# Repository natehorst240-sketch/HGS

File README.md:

# HGS-Linux

A Linux/cross-platform re-implementation of the **Agusta A109S / A109N HGS**
ground-station software (`Hgs_cpp.exe`, MFC-era Windows app) that reads IDS/DAU
downloads from the aircraft.

## Status

The `.HG*` download file format has been **reverse-engineered and verified
value-for-value against the original application** (see [FORMAT.md](FORMAT.md)):

| Section | Status |
|---------|--------|
| Parameter catalog (exceedance/fault dictionary) | decoded |
| Fault Log (first/last occurrence, count) | decoded, 16/16 events verified |
| AFCS Fault Log | decoded |
| Cumulative Log (flights, TSN/TBO, cycle counts, chip D.A., ...) | decoded, 43/43 fields verified |
| Power Assurance Log | decoded, record verified (stored fields; app-side "Calc" columns are computed, not stored) |
| Time History (1 Hz N1/N2/TRQ/TOT/CLP/NR) | decoded, verified |
| Exceedance *event* records (Max Peak/Duration) | layout unknown — need a download containing a real exceedance |
| IDS Status Log | not present in sample |
| **Live serial download protocol (9600,n,8,1)** | **fully reverse-engineered from a live capture — see reverse/PROTOCOL.md** |

## Serial protocol — DONE

Captured live from a real A109 download and validated: 25-byte space-padded
ASCII messages, stop-and-wait (downloader sends `DOWNLOAD LOGS`, DAU streams
each `.HG` record, downloader acks each with `TRANSMISSION OK`). Concatenated
records == the `.HG` file. The stick firmware (`firmware/dau_protocol.py`) is a
complete, real implementation — replayed against the captured frames it
reassembles the download byte-for-byte (589,237 bytes, exact match). Spec in
`reverse/PROTOCOL.md`; capture tools in `reverse/frida/`.

Key encoding facts: everything numeric is **BCD**; labels are 25-byte
space-padded ASCII; sequence IDs are the only plain big-endian uint16s.

## Layout

- `hgs/hg6.py` — the download-file parser (the important part)
- `hgs/ui.py` — PySide6 viewer with the original app's seven Data View tabs
- `hgs/protocol.py` — serial download state-machine skeleton (`TODO(protocol)`)
- `hgs/config.py` — INI config replacing the original's registry keys
- `FORMAT.md` — byte-level file-format specification
- `sandbox/` — Wine sandbox for the original `.exe` on Linux: `setup.sh`, `run.sh --tap /dev/ttyUSB0` or `--sim` (serial tap + DAU simulator, `--wireshark` live), `sniff.py` terminal sniffer, `wireshark/hgs.lua` dissector, `selftest.py`
- `sample-data/` — a real download (S/N 22366) + decoded CSV exports

## Run (Linux)

```bash
python3 -m venv .venv && source .venv/bin/activate
pip install -r requirements.txt
python -m hgs        # File -> Open -> sample-data/22366_260707_A1.HG6
```

Parsing works headless too:

```python
from hgs import hg6
p = hg6.parse_file("sample-data/22366_260707_A1.HG6")
print(p.cumulative, p.faults, len(p.time_history))
```

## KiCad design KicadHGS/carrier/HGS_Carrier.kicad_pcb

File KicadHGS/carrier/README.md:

# HGS Download Stick — RS-232 carrier

Pico-format carrier that sits under the **Waveshare ESP32-S3-Touch-LCD-1.9
(SKU 30939)** and gives it a DE9 RS-232 port for the A109 DAU maintenance
connector.

> **This revision is a deliberately minimal 3-wire MAX3232 straight-through.**
> An earlier design had jumpers (JP1–JP3), a 2N7002 for FUNCTION SEL, D1/D2 TVS,
> 47 Ω series resistors, and a CTS sense line. Those were **removed** — the real
> captured download is plain 3-wire stop-and-wait (see `../../reverse/PROTOCOL.md`),
> so none of them are needed. If you're reading an older description mentioning
> jumpers/MOSFET/TVS, it's stale; the netlist below is the truth.

| File | What it is |
|---|---|
| `HGS_Carrier.kicad_sch` | the schematic — open this |
| `HGS_Carrier.kicad_sym` | project symbol for the module (40 pins, real ESP32 names) |
| `gen_schematic.py` | generator that produced the schematic — edit this, not the .kicad_sch |
| `bom.csv`, `net.net`, `erc.rpt` | exports, regenerate any time with `kicad-cli` |
| `upstream/` | mtguerreiro's MAX3232 sheet + licence (see Attribution) |

## The circuit (as actually netlisted)

Verified from `net.net`, not the prose:

```
ESP32-S3-Touch-LCD-1.9 (J1)     MAX3232 (U1) on 3V3        DE9 (J2, male DTE)
  IO16  (J1 pin 15) ----------- T1IN(11) -> T1OUT(14) ---- pin 3  TXD  -> DAU RXD
  IO18  (J1 pin 17) <----------- R1OUT(12) <- R1IN(13) ---- pin 2  RXD  <- DAU TXD
  GND (all 8 module GND) ------- GND(15) ----------------- pin 5  GND + shell
  3V3   (J1 pin 36) ----------- VCC(16)
```

- **U1 MAX3232**, VCC on **+3V3 only** (never 5 V — the S3 is not 5 V tolerant),
  charge-pump caps **C1–C5 100 nF** (C1±, C2±, V+, V−).
- **9600 baud, 8N1** (`Serial1.begin(9600, SERIAL_8N1, RX=IO18, TX=IO16)` in
  firmware) — matches the original app's `9600,n,8,1`.
- The firmware uses **Serial1 on IO16/IO18**, a second UART. Do **not** move it to
  IO43/IO44 (UART0, header pins 1/2): the ROM bootloader prints its 115200 banner
  there at power-up, straight into the DAU.
- MAX3232 **second channel (T2/R2) is unused and unconnected** — no FUNCTION SEL
  driver, no CTS sense on this revision (see below).

## Cable pinout — standard DTE serial

The maintenance cable presents a **standard DTE serial port** (the same pinout a
generic USB-to-serial adapter uses, which is how the HGS laptop connected). The
board is straight-through, male DE9:

| DE9 pin | Signal | Our side |
|---|---|---|
| 2 | RXD | receive ← MAX3232 R1IN |
| 3 | TXD | transmit → MAX3232 T1OUT |
| 5 | GND | signal return |
| 1/4/6/7/8/9 | — | **not connected** |

## FUNCTION SEL — open item (resolve by test, not by adding parts)

The A109 maintenance connector (J101-E) carries a **FUNCTION SEL** discrete that
*may* need to be asserted before the DAU will stream. **This board does not drive
it** (DE9 pin 4 and IO15 are unconnected) — a deliberate simplification.

Resolve it empirically:
1. Build the board and run a real download. If the DAU streams, FUNCTION SEL was
   not needed — done.
2. If the DAU stays silent, buzz out the working HGS laptop/USB-serial cable to
   see whether it drives DTR (pin 4) or RTS (pin 7). Only then add a driver:
   route `IO15 → MAX3232 T2IN → T2OUT → DE9 pin 4` (one edit in
   `gen_schematic.py`) and set `USE_FUNCTION_SEL = true` in firmware.

`USE_FUNCTION_SEL` stays `false` until confirmed.

## Verified

Regenerate before ordering (numbers change with the design — don't trust a stale
copy):

```bash
cd KicadHGS/carrier && python gen_schematic.py       # regenerates schematic + exports
kicad-cli sch erc HGS_Carrier.kicad_sch              # run ERC
```

Real nets in the current design: `+3V3, GND, /DAU_TX_TTL, /DAU_RX_TTL, /DE9_P2,
/DE9_P3, /V_PLUS, /V_MINUS, /C1P, /C1N, /C2P, /C2N` — everything else is an
explicit no-connect.

## BOM (current, minimal)

| Ref | Value | Footprint |
|---|---|---|
| U1 | MAX3232 | SOIC-16 |
| C1–C5 | 100 nF | 0603 |
| J1 | ESP32-S3-Touch-LCD-1.9 header | RaspberryPi_Pico_Common_THT |
| J2 | DE9 male | DSUB-9 horizontal |

(The older `HGS_Carrier.csv` still lists JP1–JP3/Q1/D1/D2/R1–R4 from the previous
design — ignore it; `fab/HGS_Carrier_BOM.csv` is the current one.)

## Reuse rather than authored

- **Header footprint:** `Module:RaspberryPi_Pico_Common_THT` (ships with KiCad).
  Verified against Waveshare's dimension drawing: 2.54 mm pitch, 17.78 mm row
  spacing, 48.26 mm pin 1→20 span — exact match.
- **MAX3232 section:** topology follows `mtguerreiro/pcbs` (BSD-3-Clause). See
  Attribution. (The 47 Ω series resistors from that reference were dropped here.)
- **Everything else** is stock KiCad symbols.

## Layout notes

- **Do not use header pins 1/2** (IO43/IO44 = UART0) for the serial port.
- Module PCB is **52.60 × 29.00 mm**; the bezel is **55.00 × 31.40 mm** and
  overhangs ~1.2 mm per side. M2 mounting holes on a **40.75 × 25.00 mm**
  rectangle. The Pico footprint's silk outline is a 51.0 × 21.0 Pico — redraw it.
- The DE9 flange (~30.8 mm) is wider than the board. Bolt its jackscrews to the
  enclosure so the connector carries the hanging load, not the PCB.
- Optional: TVS on RX/TX for flight-line transients (footprints not on this
  revision; add if the environment warrants).
- **Print the layout 1:1 and test-fit the real module before ordering. Order one
  board first.**

## Regenerating

```bash
cd KicadHGS/carrier && python gen_schematic.py
```

Connectivity is by net label, placed programmatically on each pin's exact
connection point using geometry from KiCad's own libraries — this rules out the
hand-drawn failure of a label one grid step off a pin. Edit `gen_schematic.py`
and re-run rather than hand-editing the `.kicad_sch`. (This README is hand-written
and safe to edit directly.)

## Attribution

The MAX3232 section derives from **[mtguerreiro/pcbs](https://github.com/mtguerreiro/pcbs)**,
`pi-pico-itm39xxc-if/ttl_rs232_max3232.kicad_sch`, **BSD-3-Clause**. The original
sheet and licence text are preserved verbatim in `upstream/`.

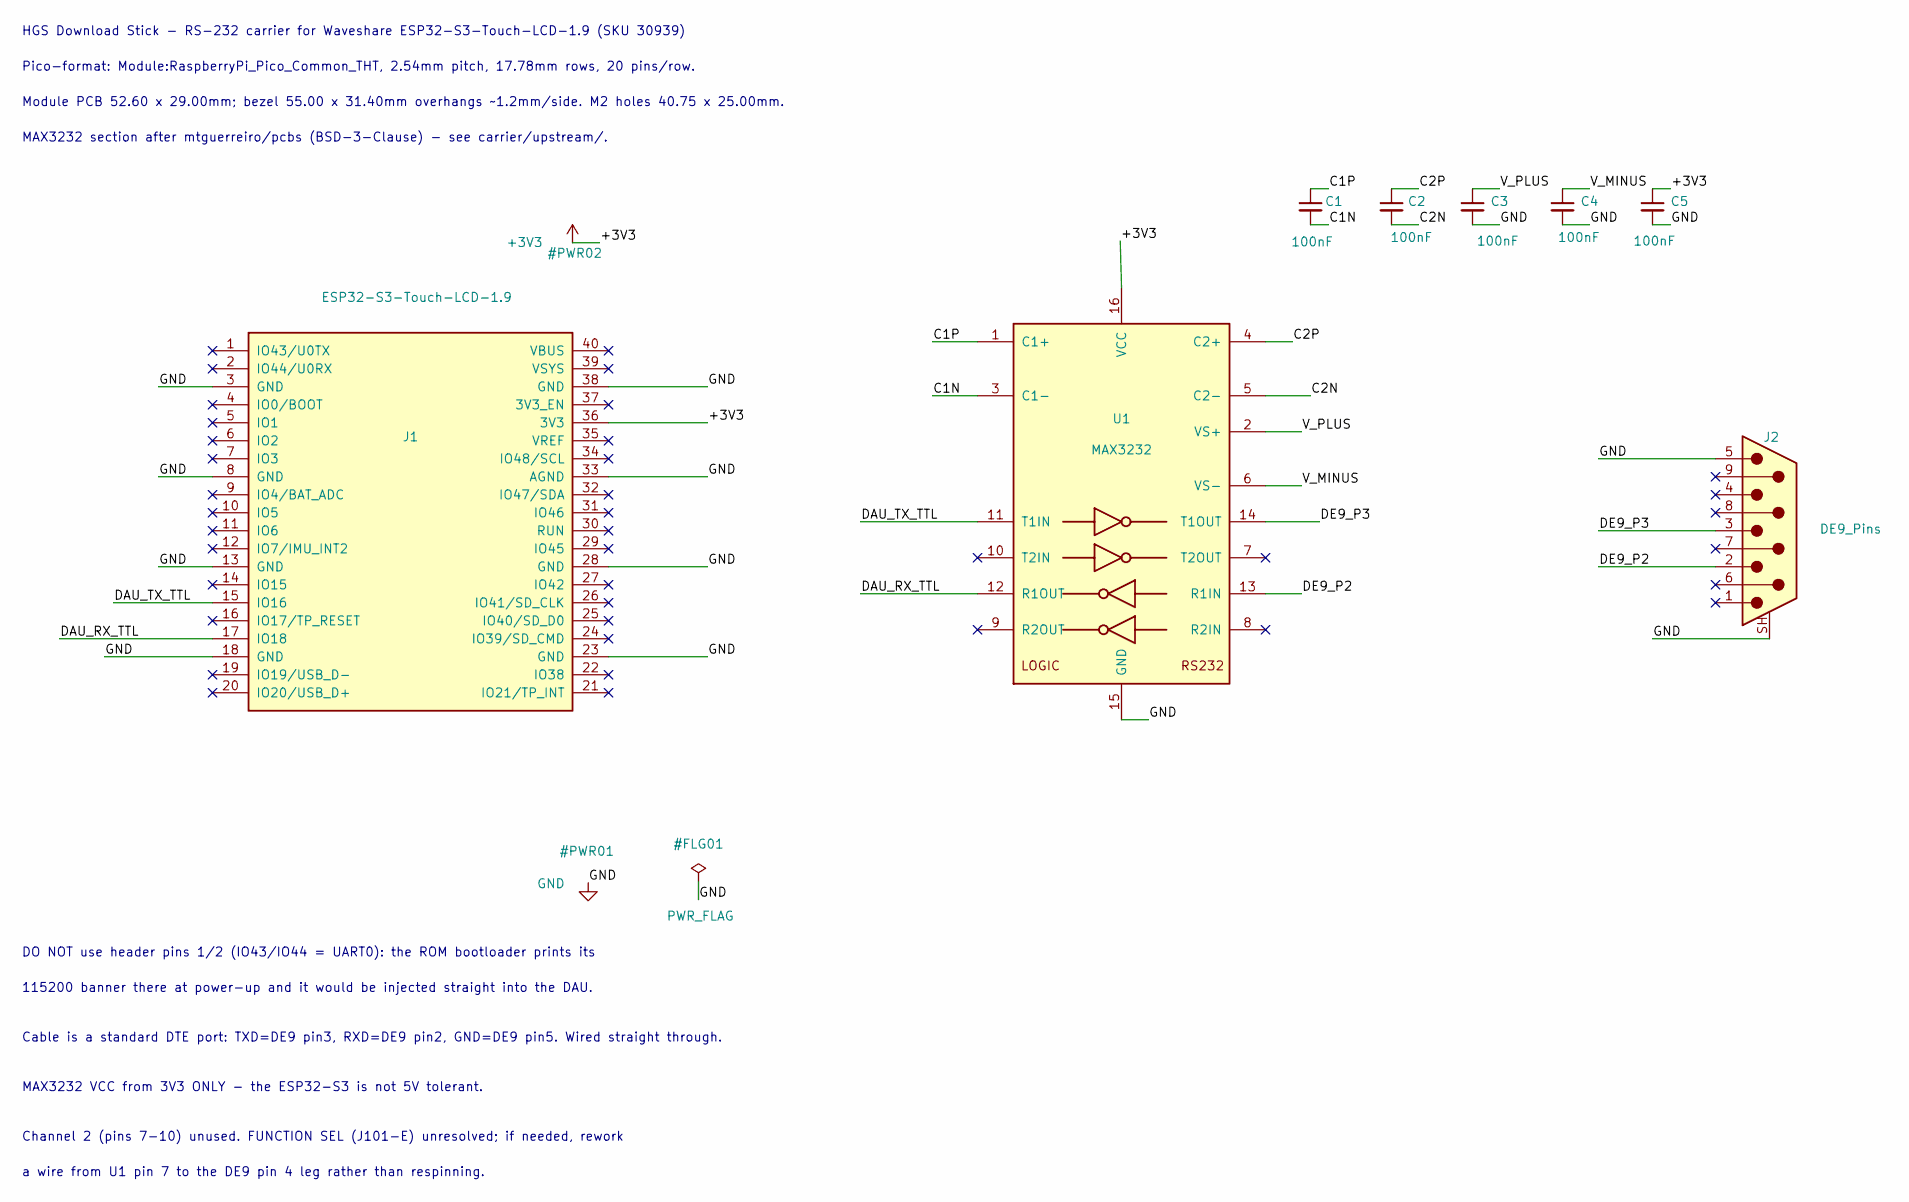
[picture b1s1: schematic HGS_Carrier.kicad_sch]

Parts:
C1, C2, C3, C4, C5: 100nF; C_0603_1608Metric
J1: ESP32-S3-Touch-LCD-1.9; RaspberryPi_Pico_Common_THT
J2: DE9_Pins; DSUB-9_Pins_Horizontal_P2.77x2.84mm_EdgePinOffset4.94mm_Hou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
U1: MAX3232; SOIC-16_3.9x9.9mm_P1.27mm

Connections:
+3V3: C5.1, J1.36 (3V3), U1.16 (VCC)
/C1N: C1.2, U1.3 (C1-)
/C1P: C1.1, U1.1 (C1+)
/C2N: C2.2, U1.5 (C2-)
/C2P: C2.1, U1.4 (C2+)
/DAU_RX_TTL: J1.17 (IO18), U1.12 (R1OUT)
/DAU_TX_TTL: J1.15 (IO16), U1.11 (T1IN)
/DE9_P2: J2.2, U1.13 (R1IN)
/DE9_P3: J2.3, U1.14 (T1OUT)
/V_MINUS: C4.1, U1.6 (VS-)
/V_PLUS: C3.1, U1.2 (VS+)
GND: C3.2, C4.2, C5.2, J1.3 (GND), J1.8 (GND), J1.13 (GND), J1.18 (GND), J1.23 (GND), J1.28 (GND), J1.33 (AGND), J1.38 (GND), J2.5, J2.SH (PAD), U1.15 (GND)

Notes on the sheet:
Channel 2 (pins 7-10) unused. FUNCTION SEL (J101-E) unresolved; if needed, rework
Pico-format: Module:RaspberryPi_Pico_Common_THT, 2.54mm pitch, 17.78mm rows, 20 pins/row.
MAX3232 VCC from 3V3 ONLY - the ESP32-S3 is not 5V tolerant.
MAX3232 section after mtguerreiro/pcbs (BSD-3-Clause) - see carrier/upstream/.
DO NOT use header pins 1/2 (IO43/IO44 = UART0): the ROM bootloader prints its
HGS Download Stick - RS-232 carrier for Waveshare ESP32-S3-Touch-LCD-1.9 (SKU 30939)
a wire from U1 pin 7 to the DE9 pin 4 leg rather than respinning.
Module PCB 52.60 x 29.00mm; bezel 55.00 x 31.40mm overhangs ~1.2mm/side. M2 holes 40.75 x 25.00mm.
115200 banner there at power-up and it would be injected straight into the DAU.
Cable is a standard DTE port: TXD=DE9 pin3, RXD=DE9 pin2, GND=DE9 pin5. Wired straight through.

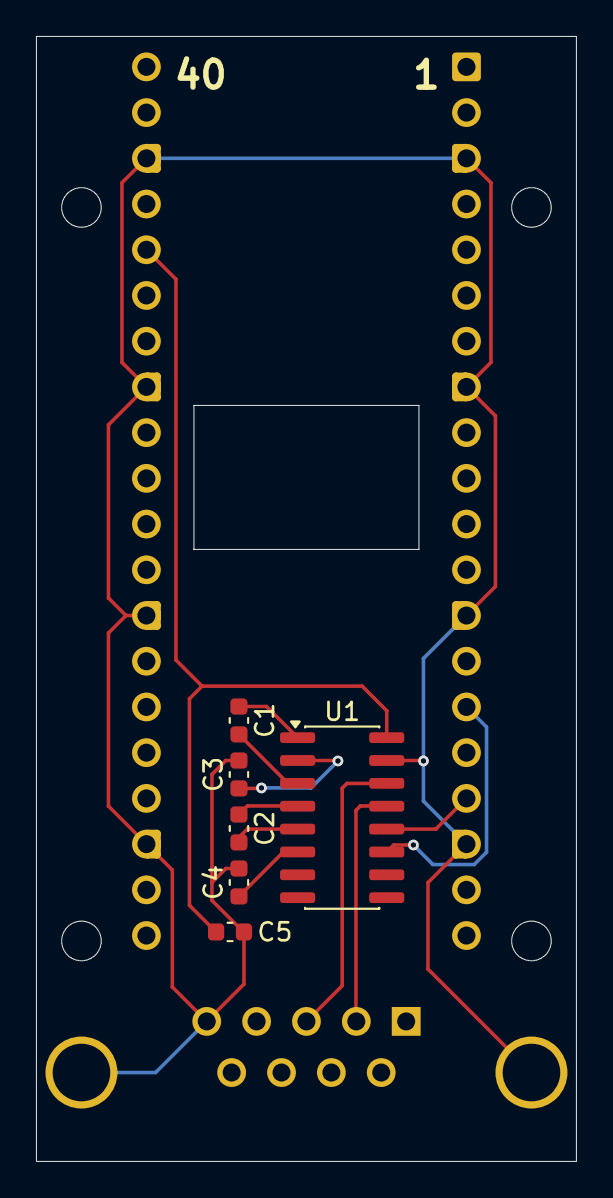
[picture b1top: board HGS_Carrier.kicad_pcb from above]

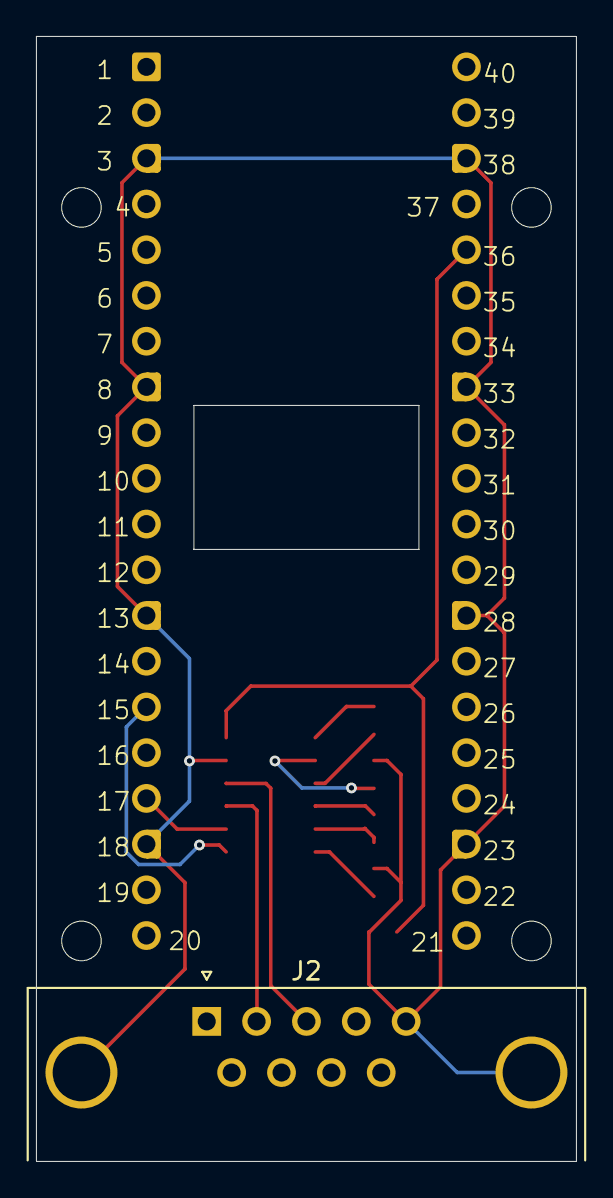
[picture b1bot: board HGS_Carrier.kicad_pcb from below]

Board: 2 copper layers, 30.0 x 62.5 mm, 12 parts (2 on the bottom side), 12 nets.

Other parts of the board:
MountingHole, MountingHole1, MountingHole2, MountingHole3: MountingHole_2.2mm_M2

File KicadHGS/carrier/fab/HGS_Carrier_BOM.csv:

"Designator","Value","Footprint","Qty"
"C1-C5","100nF","Capacitor_SMD:C_0603_1608Metric","5"
"J1","ESP32-S3-Touch-LCD-1.9","Module:RaspberryPi_Pico_Common_THT","1"
"J2","DE9_Pins","Connector_Dsub:DSUB-9_Pins_Horizontal_P2.77x2.84mm_EdgePinOffset4.94mm_Housed_MountingHolesOffset4.94mm","1"
"U1","MAX3232","Package_SO:SOIC-16_3.9x9.9mm_P1.27mm","1"

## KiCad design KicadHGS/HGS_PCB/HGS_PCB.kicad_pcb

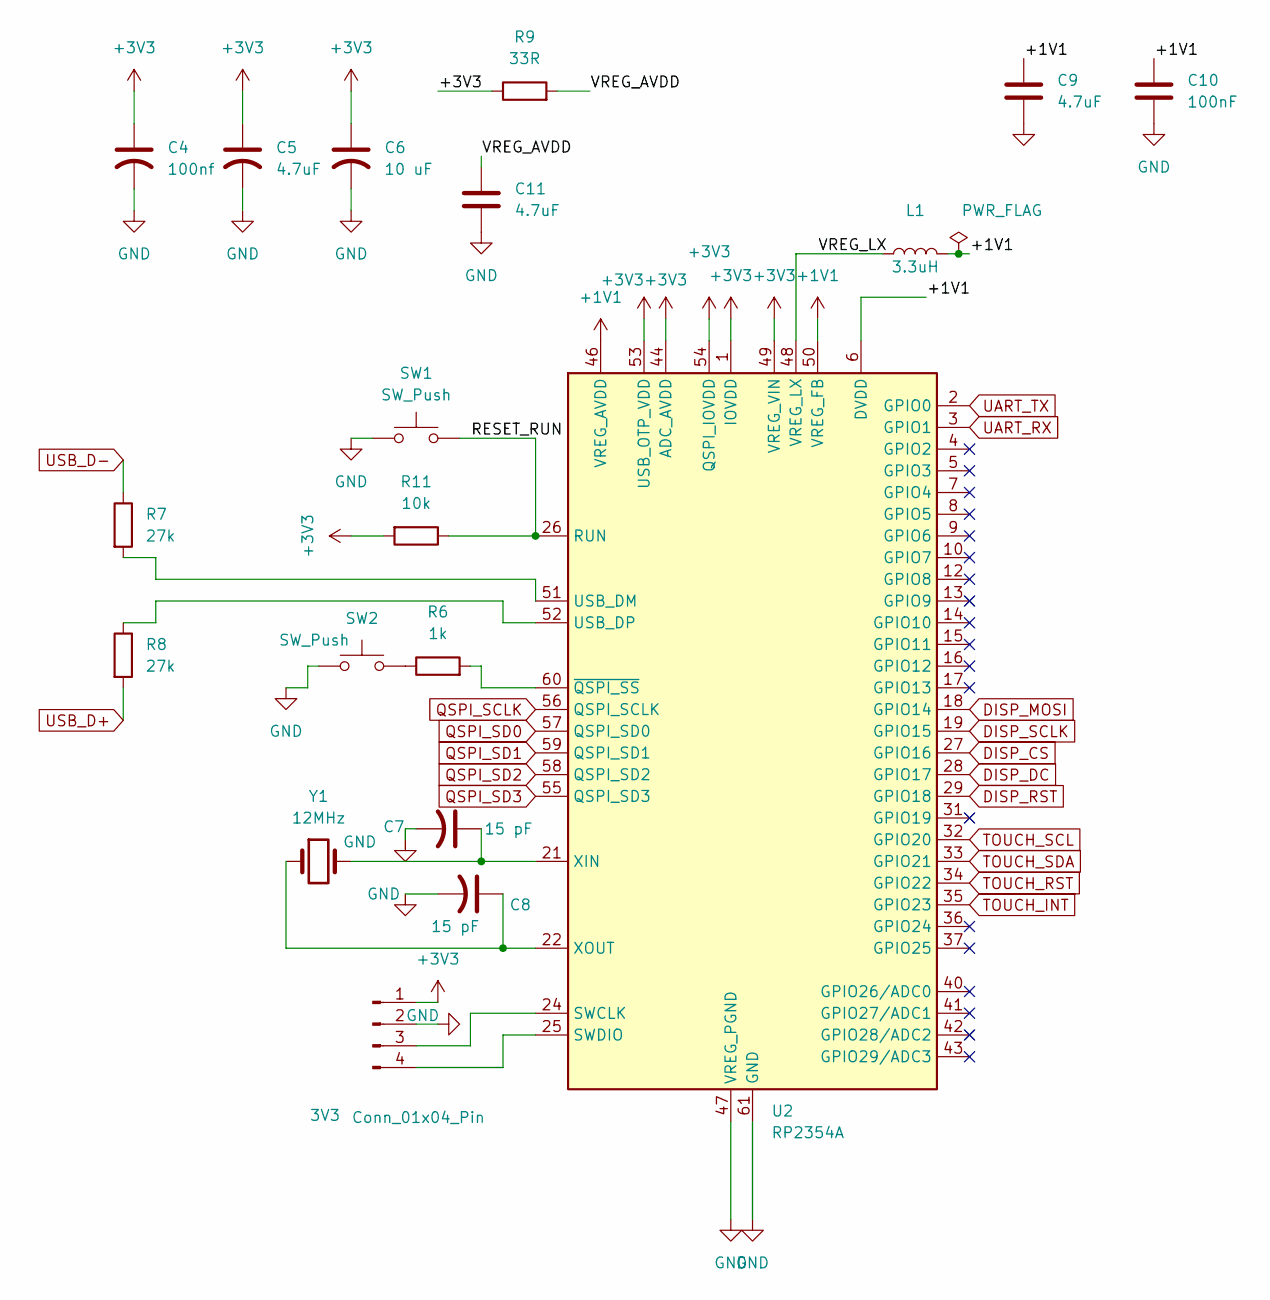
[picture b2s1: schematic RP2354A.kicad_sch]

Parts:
3V3: Conn_01x04_Pin; JST_EH_B4B-EH-A_1x04_P2.50mm_Vertical
C4: 100nf; C_0603_1608Metric
C5, C9, C11: 4.7uF; C_0805_2012Metric
C6: 10 uF; C_0805_2012Metric
C7, C8: 15 pF; C_0603_1608Metric
C10: 100nF; C_0603_1608Metric
L1: 3.3uH; L_Wuerth_MAPI-3015
R6: 1k; R_0603_1608Metric_Pad0.98x0.95mm_HandSolder
R7, R8: 27k; R_0603_1608Metric_Pad0.98x0.95mm_HandSolder
R9: 33R; R_0603_1608Metric_Pad0.98x0.95mm_HandSolder
R11: 10k; R_0603_1608Metric_Pad0.98x0.95mm_HandSolder
SW1, SW2: SW_Push; SW_PUSH_6mm
U2: RP2354A; QFN-60-1EP_7x7mm_P0.4mm_EP3.4x3.4mm
Y1: 12MHz; Crystal_HC49-U_Horizontal

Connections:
+1V1: C9.1, C10.1, L1.2, U2.6 (DVDD), U2.23 (DVDD), U2.39 (DVDD), U2.46 (VREG_AVDD), U2.50 (VREG_FB)
+3V3: 3V3.1, C4.1, C5.1, C6.1, R9.1, R11.2, U2.1 (IOVDD), U2.11 (IOVDD), U2.20 (IOVDD), U2.30 (IOVDD), U2.38 (IOVDD), U2.44 (ADC_AVDD), U2.45 (IOVDD), U2.49 (VREG_VIN), U2.53 (USB_OTP_VDD), U2.54 (QSPI_IOVDD); also elsewhere on the board
/MCU-RP2354A/RESET_RUN: R11.1, SW1.2, U2.26 (RUN)
/MCU-RP2354A/VREG_AVDD: C11.1, R9.2
/MCU-RP2354A/VREG_LX: L1.1, U2.48 (VREG_LX)
DISP_CS: U2.27 (GPIO16); also elsewhere on the board
DISP_DC: U2.28 (GPIO17); also elsewhere on the board
DISP_MOSI: U2.18 (GPIO14); also elsewhere on the board
DISP_RST: U2.29 (GPIO18); also elsewhere on the board
DISP_SCLK: U2.19 (GPIO15); also elsewhere on the board
GND: 3V3.2, C4.2, C5.2, C6.2, C7.2, C8.2, C9.2, C10.2, C11.2, SW1.1, SW2.1, U2.47 (VREG_PGND), U2.61 (GND); also elsewhere on the board
unnamed: 3V3.3, U2.24 (SWCLK)
unnamed: 3V3.4, U2.25 (SWDIO)
unnamed: R6.1, SW2.2
unnamed: R7.2, U2.51 (USB_DM)
unnamed: R8.1, U2.52 (USB_DP)
unnamed: C7.1, U2.21 (XIN), Y1.2
unnamed: C8.1, U2.22 (XOUT), Y1.1
unnamed: R6.2, U2.60 (~QSPI_SS)
QSPI_SCLK: U2.56 (QSPI_SCLK); also elsewhere on the board
QSPI_SD0: U2.57 (QSPI_SD0); also elsewhere on the board
QSPI_SD1: U2.59 (QSPI_SD1); also elsewhere on the board
QSPI_SD2: U2.58 (QSPI_SD2); also elsewhere on the board
QSPI_SD3: U2.55 (QSPI_SD3); also elsewhere on the board
TOUCH_INT: U2.35 (GPIO23); also elsewhere on the board
TOUCH_RST: U2.34 (GPIO22); also elsewhere on the board
TOUCH_SCL: U2.32 (GPIO20); also elsewhere on the board
TOUCH_SDA: U2.33 (GPIO21); also elsewhere on the board
UART_RX: U2.3 (GPIO1); also elsewhere on the board
UART_TX: U2.2 (GPIO0); also elsewhere on the board
USB_D+: R8.2; also elsewhere on the board
USB_D-: R7.1; also elsewhere on the board

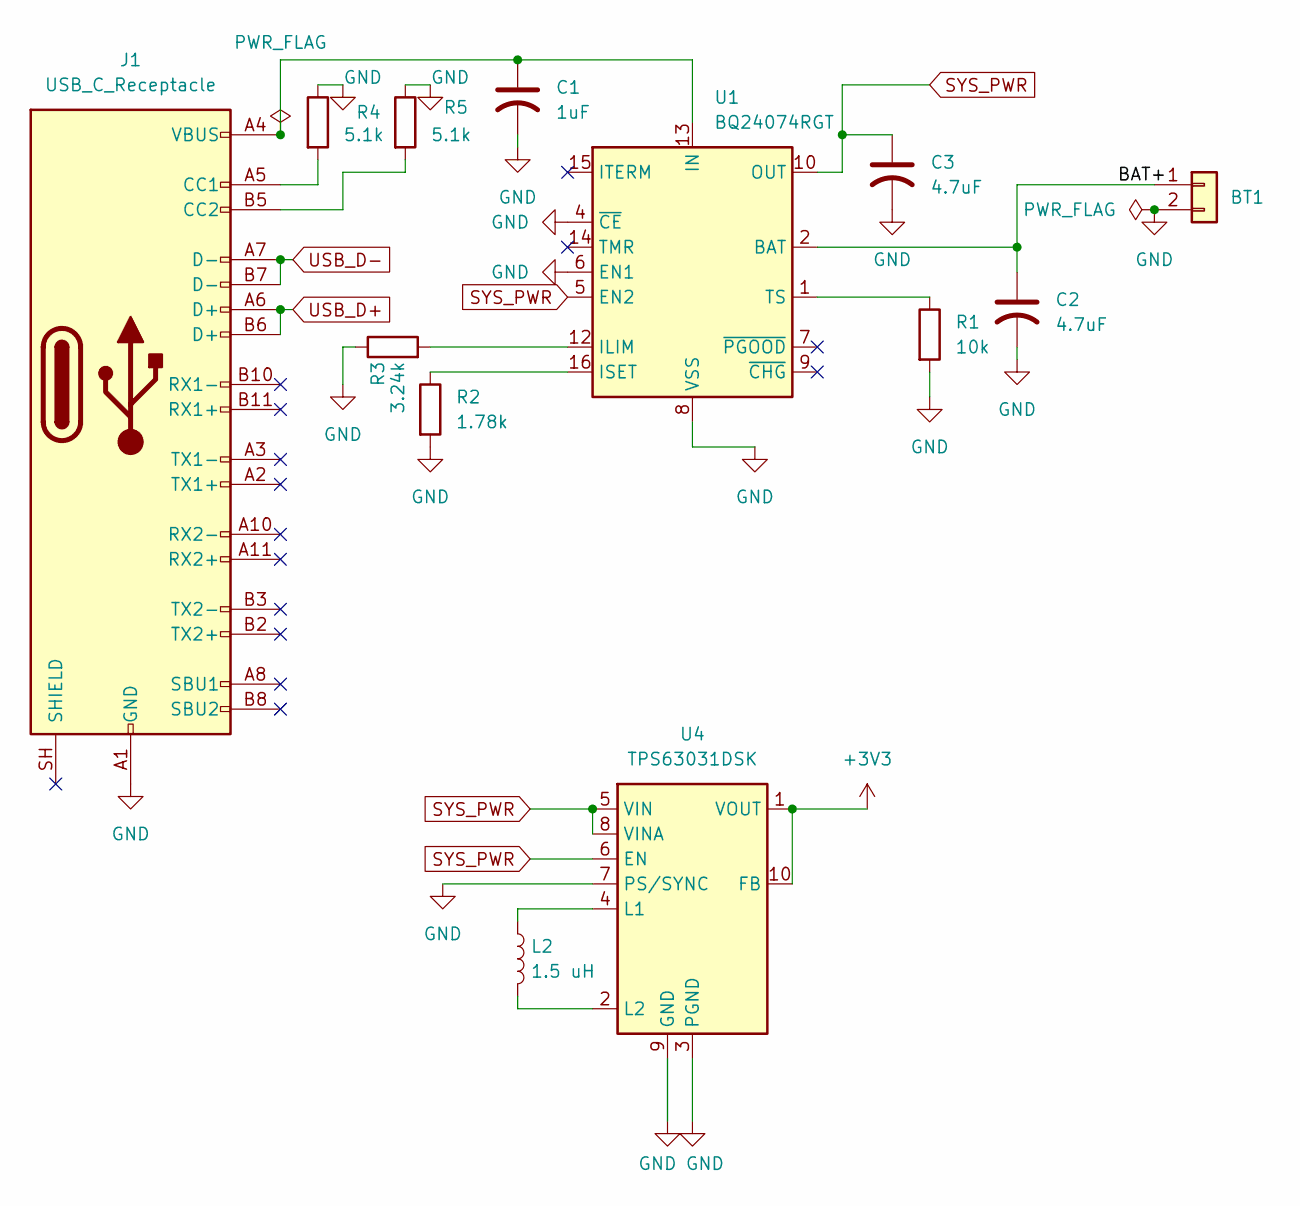
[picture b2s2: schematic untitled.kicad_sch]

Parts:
BT1: BatteryHolder_Keystone_2460_1xAA
C1: 1uF; C_0603_1608Metric
C2, C3: 4.7uF; C_0603_1608Metric
J1: USB_C_Receptacle; USB_C_Receptacle_GCT_USB4085
L2: 1.5 uH; L_Wuerth_MAPI-3015
R1: 10k; R_0603_1608Metric_Pad0.98x0.95mm_HandSolder
R2: 1.78k; R_0603_1608Metric_Pad0.98x0.95mm_HandSolder
R3: 3.24k; R_0603_1608Metric_Pad0.98x0.95mm_HandSolder
R4, R5: 5.1k; R_0603_1608Metric_Pad0.98x0.95mm_HandSolder
U1: BQ24074RGT; VQFN-16-1EP_3x3mm_P0.5mm_EP1.6x1.6mm
U4: TPS63031DSK; WSON-10-1EP_2.5x2.5mm_P0.5mm_EP1.2x2mm

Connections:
+3V3: U4.1 (VOUT), U4.10 (FB); also elsewhere on the board
/14450_BAT_POWER/BAT+: BT1.1, C2.1, U1.2 (BAT), U1.3 (BAT)
GND: BT1.2, C1.2, C2.2, C3.2, J1.A1 (GND), J1.A12 (GND), J1.B1 (GND), J1.B12 (GND), R1.2, R2.2, R3.1, R4.1, R5.1, U1.4 (~CE), U1.6 (EN1), U1.8 (VSS), U1.17 (VSS), U4.3 (PGND), U4.7 (PS/SYNC), U4.9 (GND), U4.11 (PGND); also elsewhere on the board
unnamed: J1.A5 (CC1), R4.2
unnamed: J1.B5 (CC2), R5.2
unnamed: R3.2, U1.12 (ILIM)
unnamed: C1.1, J1.A4 (VBUS), J1.A9 (VBUS), J1.B4 (VBUS), J1.B9 (VBUS), U1.13 (IN)
unnamed: R2.1, U1.16 (ISET)
unnamed: R1.1, U1.1 (TS)
unnamed: L2.1, U4.4 (L1)
unnamed: L2.2, U4.2 (L2)
SYS_PWR: C3.1, U1.5 (EN2), U1.10 (OUT), U1.11 (OUT), U4.5 (VIN), U4.6 (EN), U4.8 (VINA)
USB_D+: J1.A6 (D+), J1.B6 (D+); also elsewhere on the board
USB_D-: J1.A7 (D-), J1.B7 (D-); also elsewhere on the board

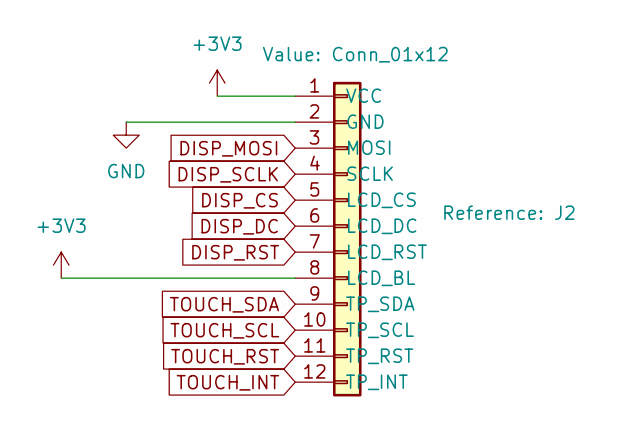
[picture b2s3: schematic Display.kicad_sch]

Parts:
J2: Conn_01x12; JST_GH_BM12B-GHS-TBT_1x12-1MP_P1.25mm_Vertical

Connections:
+3V3: J2.1 (VCC), J2.8 (LCD_BL); also elsewhere on the board
DISP_CS: J2.5 (LCD_CS); also elsewhere on the board
DISP_DC: J2.6 (LCD_DC); also elsewhere on the board
DISP_MOSI: J2.3 (MOSI); also elsewhere on the board
DISP_RST: J2.7 (LCD_RST); also elsewhere on the board
DISP_SCLK: J2.4 (SCLK); also elsewhere on the board
GND: J2.2 (GND); also elsewhere on the board
TOUCH_INT: J2.12 (TP_INT); also elsewhere on the board
TOUCH_RST: J2.11 (TP_RST); also elsewhere on the board
TOUCH_SCL: J2.10 (TP_SCL); also elsewhere on the board
TOUCH_SDA: J2.9 (TP_SDA); also elsewhere on the board

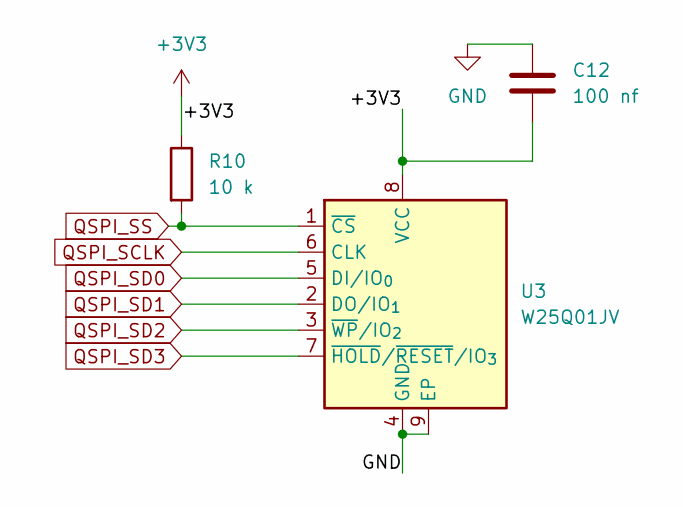
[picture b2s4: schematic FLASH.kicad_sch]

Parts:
C12: 100 nf; C_0603_1608Metric
R10: 10 k; R_0603_1608Metric_Pad0.98x0.95mm_HandSolder
U3: W25Q01JV; WSON-8-1EP_6x5mm_P1.27mm_EP3.4x4.3mm

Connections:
+3V3: C12.2, R10.1, U3.8 (VCC); also elsewhere on the board
GND: C12.1, U3.4 (GND), U3.9 (EP); also elsewhere on the board
QSPI_SCLK: U3.6 (CLK); also elsewhere on the board
QSPI_SD0: U3.5 (DI/IO_{0}); also elsewhere on the board
QSPI_SD1: U3.2 (DO/IO_{1}); also elsewhere on the board
QSPI_SD2: U3.3 (~WP/IO_{2}); also elsewhere on the board
QSPI_SD3: U3.7 (~HOLD/~RESET/IO_{3}); also elsewhere on the board
QSPI_SS: R10.2, U3.1 (~CS)

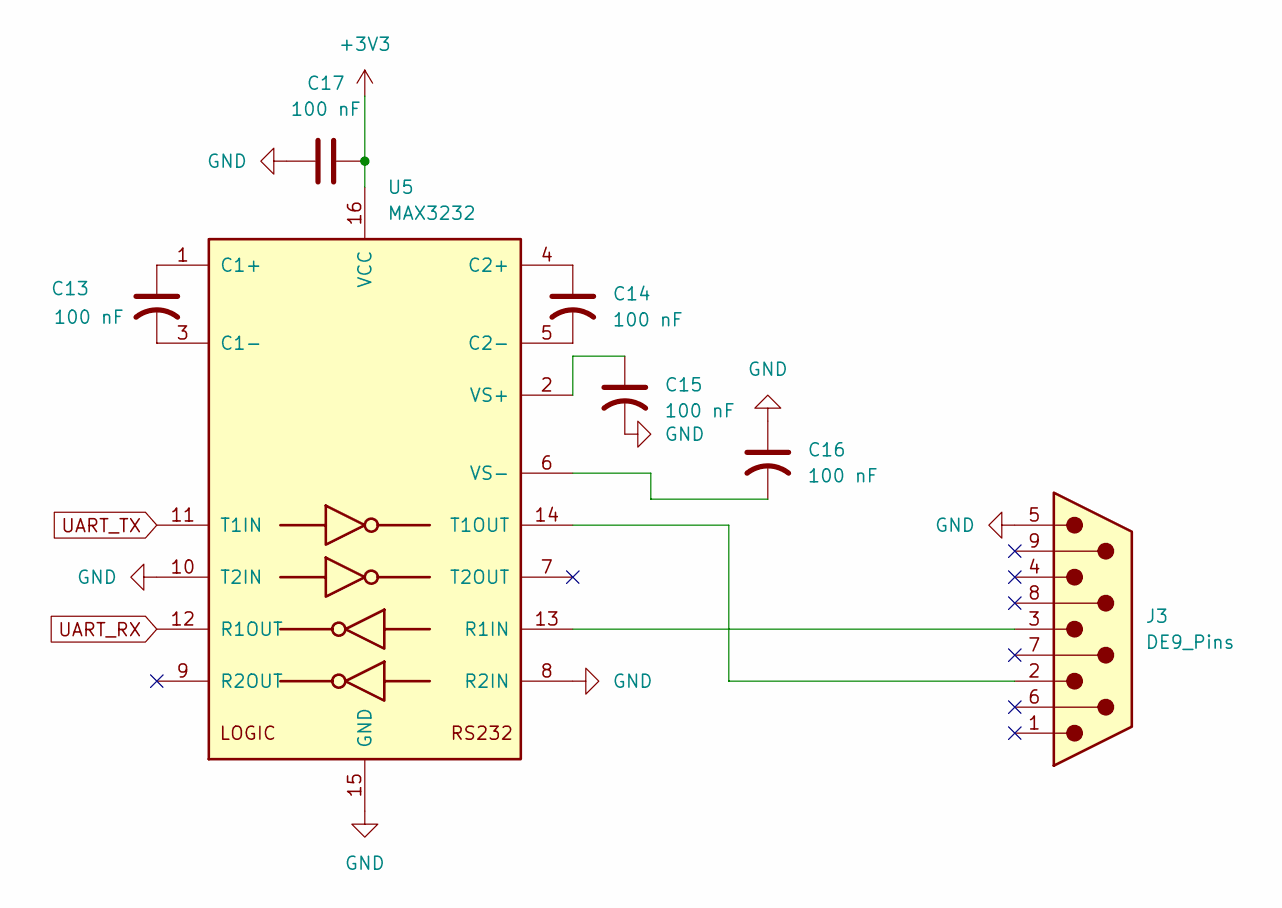
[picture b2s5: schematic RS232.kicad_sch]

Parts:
C13, C14, C15, C16, C17: 100 nF; C_0603_1608Metric
J3: DE9_Pins; DSUB-9_Pins_Horizontal_P2.77x2.84mm_EdgePinOffset14.56mm_Ho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
U5: MAX3232; SOIC-16_3.9x9.9mm_P1.27mm

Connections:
+3V3: C17.2, U5.16 (VCC); also elsewhere on the board
GND: C15.2, C16.1, C17.1, J3.5, U5.8 (R2IN), U5.10 (T2IN), U5.15 (GND); also elsewhere on the board
unnamed: C13.1, U5.1 (C1+)
unnamed: C13.2, U5.3 (C1-)
unnamed: C14.1, U5.4 (C2+)
unnamed: C14.2, U5.5 (C2-)
unnamed: J3.3, U5.13 (R1IN)
unnamed: J3.2, U5.14 (T1OUT)
unnamed: C15.1, U5.2 (VS+)
unnamed: C16.2, U5.6 (VS-)
UART_RX: U5.12 (R1OUT); also elsewhere on the board
UART_TX: U5.11 (T1IN); also elsewhere on the board

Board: 2 copper layers, 43 parts (1 on the bottom side), 51 nets, no tracks yet.

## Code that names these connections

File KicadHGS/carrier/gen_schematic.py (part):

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# (ref, pin) -> net label
NETS = {
    # --- module: only what the level shifter needs ------------------------
    ("J1", "15"): "DAU_TX_TTL",      # IO16 (header pin 15) -> T1IN
    ("J1", "17"): "DAU_RX_TTL",      # IO18 (header pin 17) <- R1OUT
    ("J1", "36"): "+3V3",
    # every ground pin on the header, for a short return path
    ("J1", "3"): "GND", ("J1", "8"): "GND", ("J1", "13"): "GND",
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    ("U1", "4"): "C2P",   ("U1", "5"): "C2N",    ("U1", "6"): "V_MINUS",
    ("U1", "11"): "DAU_TX_TTL",      # T1IN  <- IO16, direct, no series R
    ("U1", "12"): "DAU_RX_TTL",      # R1OUT -> IO18, direct
    ("U1", "13"): "DE9_P2",          # R1IN  <- DE9 pin 2 (RXD)
    ("U1", "14"): "DE9_P3",          # T1OUT -> DE9 pin 3 (TXD)
    ("U1", "15"): "GND",  ("U1", "16"): "+3V3",
    # pins 7-10 (channel 2) deliberately unconnected - the captured download
    # was plain 3-wire and T2IN must not be left driven by nothing.
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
